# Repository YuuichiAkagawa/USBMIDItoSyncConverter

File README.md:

# USB MIDI to Sync Converter
Converts USB MIDI clock messages to sync signals.

[日本語版](README-ja.md)

## How to build
### Target microcontroller
- Seeed XIAO RP2040

### Build
This project uses Arduino IDE2 and requires the following libraries:
- board: [Arduino-pico](https://github.com/earlephilhower/arduino-pico) 4.1.1
- library: [Arduino MIDI Library](https://github.com/FortySevenEffects/arduino_midi_library) 5.0.2

Build setting:
- Tools->Board:->Raspberry Pi Pico/RP2040->Seed XIAO RP2040
- Tools->USB Stack:->Adafruilt TinyUSB

## Schematic
Complete schematic created in [KiCad](./hardware/KiCad/USBMIDItoSYNC_Converter/).

Minimum configuration with sync signal output terminal only

## Usage
Connects to the sending MIDI device with a USB cable and to the receiving device with a 3.5 mm stereo cable.  
The run mode switch can be used to select the action to be taken when a MIDI START/STOP message is received.

### Run mode switch
The D1 pin is assigned to mode switch. D1 is pulled up and goes High when open.

|D1 |behaviour|
|----|---------|
|Low |Sends out or stops the sync signal in conjunction with MIDI Start and Stop messages.|
|High|Free run. When MIDI Clock is received, the Sync signal is sent regardless of the playback status of the MIDI device.|

### DIN SYNC (experimental)
The DIN SYNC Start/Stop signal is output to the D2 pin.
D2 pin is assigned to 'DIN S' on the DIP switch and is connected to the RING of the Sync terminal.

### TRS MIDI In/Out (TypeA)
Transfers MIDI messages between USB MIDI and TRS MIDI.  
Note:
- SysEx is not supported.
- The clock input from TRS MIDI IN cannot be converted to a Sync signal.
  
### Setting switch
The setting switches can be used to set PPQ values and MIDI filter settings.  

|pin|name | setting             |
|---|-----|---------------------|
|D5 |MODE0|Type setting<br>L:PPQ values are changed using Setting switch. The value stored in the EEPROM is ignored.<br>H:PPQ values ​​are changed using SysEx messages. Settings are saved in EEPROM.
|D4 |MODE1|MODE0=L : PPQ selecter<br>MODE0=H : MIDI FilterSelector
|D3 |MODE2|MODE0=L : PPQ selecter<br>MODE0=H : MIDI FilterSelector

#### MODE0=0 PPQ selector
|MODE1 |MODE2 | PPQ    |
|------|------|--------|
|H(Off)|H(Off)|1       |
|H(Off)|L(On) |2       |
|L(On) |H(Off)|4       |
|L(On) |L(On) |24      |

#### MODE0=1 MIDI Filter
|MODE1 |MODE2 | Filter                                             |
|------|------|----------------------------------------------------|
|H(Off)|H(Off)|All messages are forwarded from USB to TRS MIDI Out |
|H(Off)|L(On) |Only Clock, Start, Stop, Continue are fowarded.     |
|L(On) |H(Off)|Foward only clocks                                  |
|L(On) |L(On) |N/A (Reserved)                                      |

## About the pulse width of the sync signal
In this project, the pulse width of the sync signal is set to 5 ms.  
The reason for this is that the KORG specification is 15 ms, but many other companies' devices use 5 ms.  
If you want to change this, modify the definition of ```DEFAULT_SPW``` to ```SPW_15MS``` and rebuild.

## Change the PPQ via SysEx message
The PPQ values can be changed using SysEx messages.  
You can specify a value between 1 and 24, but it will not work correctly unless it is a divisor of 24.  
The PPQ value is stored in the EEPROM at location 0x00.

|Byte[Hex] | Description                                     |
|:--------:|-------------------------------------------------|
|F0        | Exclusive Status                                |
|7E        | non realtime Universal System Exclusive Message |
|49        | Device ID                                       |
|0B        | File Reference Message                          |
|02        | Change (Select or Reselect)                     |
|nn        | PPQ : 1,2,3,4,6,8,0Ch(12),18h(24)               |
|F7        | End Of Exclusive                                |

## Change the Sync signal pulse width via SysEx message
The Sync signal pulse width can be changed using a SysEx message.  
It can be set to 5ms or 15ms.  
The Sync signal pulse width value is stored in the EEPROM at location 0x01.

|Byte[Hex] | Description                                             |
|:--------:|---------------------------------------------------------|
|F0        | Exclusive Status                                        |
|7E        | non realtime Universal System Exclusive Message         |
|49        | Device ID                                               |
|0B        | File Reference Message                                  |
|02        | Change (Select or Reselect)                             |
|nn        | Pulse Width 5ms:3Fh(63), 15ms:5Fh(95), Reserved:7Fh(127)|
|F7        | End Of Exclusive                                        |

SysEx files are stored in assets/sysex. Use as needed.

Note: The SysEx message does not define a dedicated one, but rather diverts the universal system-exclusive File Reference Message.

## License
USB MIDI to Sync Converter is open source and licensed under the [GPL3](/LICENSE) License.

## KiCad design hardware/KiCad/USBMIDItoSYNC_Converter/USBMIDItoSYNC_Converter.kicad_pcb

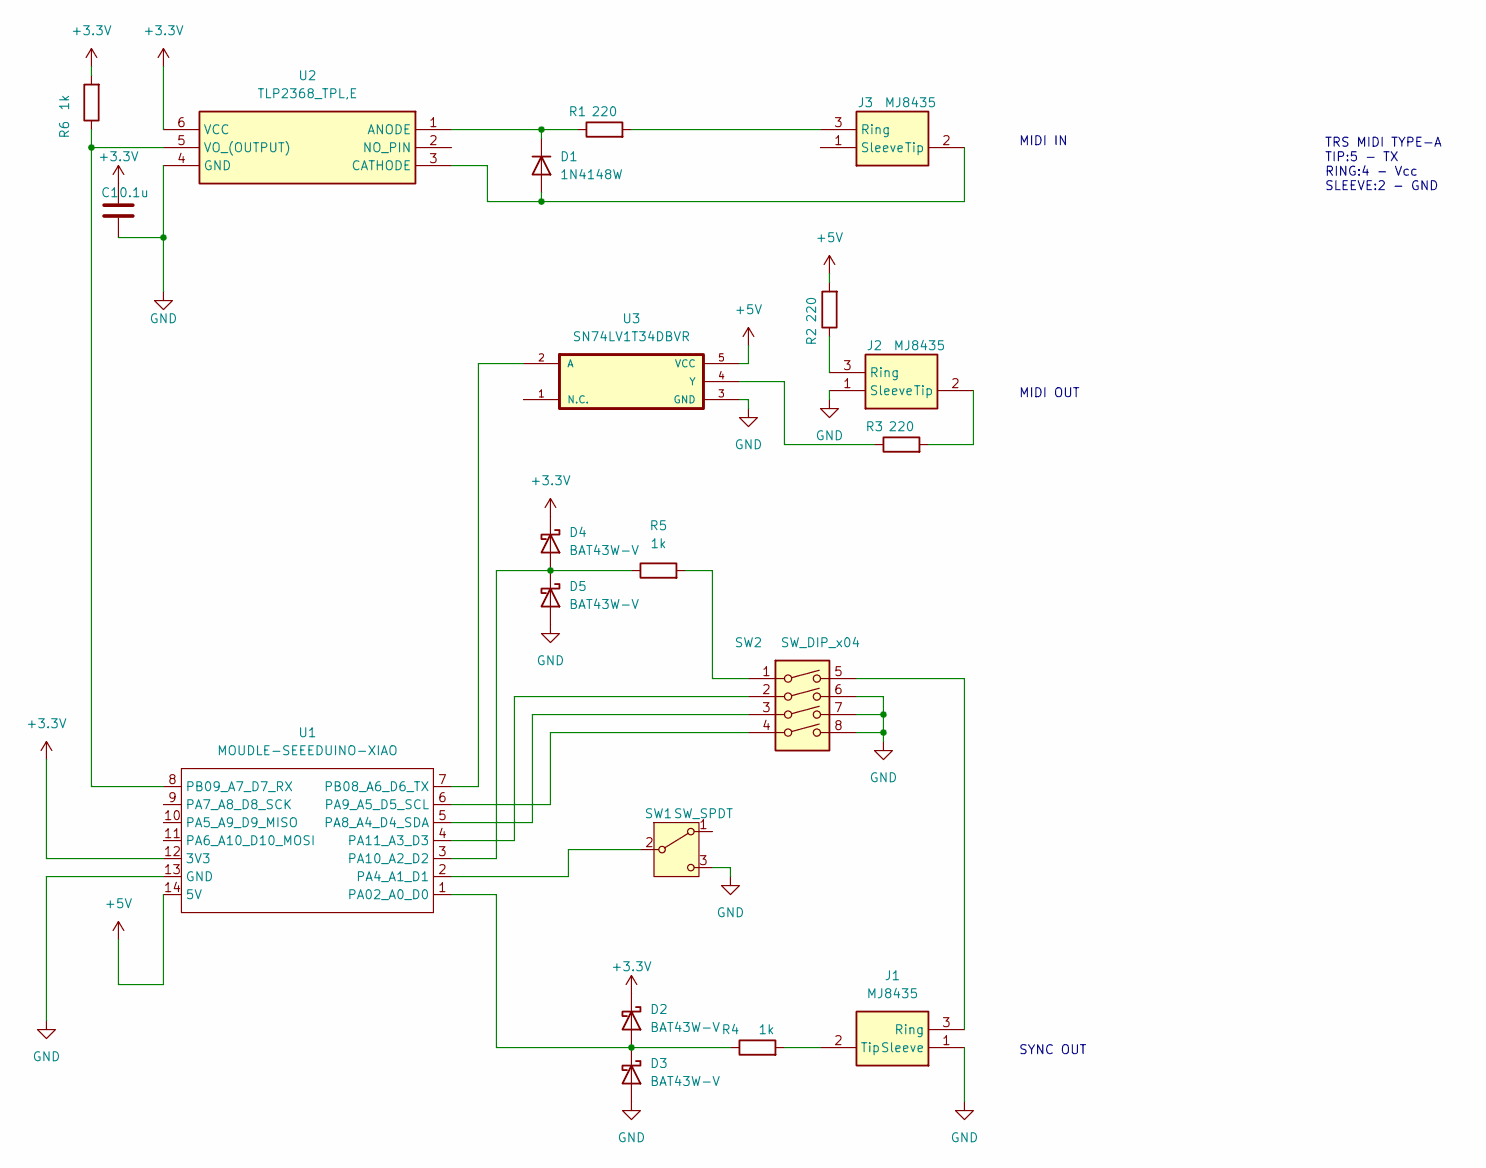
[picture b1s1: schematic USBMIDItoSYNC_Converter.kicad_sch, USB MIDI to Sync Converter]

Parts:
C1: 0.1u; C_0603_1608Metric
D1: 1N4148W; D_SOD-123
D2, D3, D4, D5: BAT43W-V; D_SOD-523
J1, J2, J3: MJ8435; Manufacturer_Part_Number MJ8435
R1, R2, R3: 220; R_0603_1608Metric
R4, R5, R6: 1k; R_0603_1608Metric
SW1: SW_SPDT; PinHeader_1x03_P2.54mm_Vertical
SW2: SW_DIP_x04; KHS42E
U1: MOUDLE-SEEEDUINO-XIAO; MOUDLE14P-XIAO-SMD-2.54-21X17.8MM
U2: TLP2368_TPL,E; SOIC127P700X230-6N; Manufacturer_Part_Number TLP2368(TPL,E; Mouser Part Number 757-TLP2368TPLE
U3: SN74LV1T34DBVR; SOT95P280X145-5N

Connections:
+3.3V: C1.1, D2.1 (K), D4.1 (K), R6.2, U1.12 (3V3), U2.6 (VCC)
+5V: R2.2, U1.14 (5V), U3.5 (VCC)
GND: C1.2, D3.2 (A), D5.2 (A), J1.1 (Sleeve), J2.1 (Sleeve), SW1.3 (C), SW2.6, SW2.7, SW2.8, U1.13 (GND), U2.4 (GND), U3.3 (GND)
unnamed: D1.2 (A), J3.2 (Tip), U2.3 (CATHODE)
unnamed: D1.1 (K), R1.1, U2.1 (ANODE)
unnamed: D2.2 (A), D3.1 (K), R4.1, U1.1 (PA02_A0_D0)
unnamed: D4.2 (A), D5.1 (K), R5.1, U1.3 (PA10_A2_D2)
unnamed: J1.3 (Ring), SW2.5
unnamed: J1.2 (Tip), R4.2
unnamed: J2.3 (Ring), R2.1
unnamed: J2.2 (Tip), R3.2
unnamed: J3.3 (Ring), R1.2
unnamed: R5.2, SW2.1
unnamed: SW1.2 (B), U1.2 (PA4_A1_D1)
unnamed: SW2.3, U1.5 (PA8_A4_D4_SDA)
unnamed: SW2.4, U1.6 (PA9_A5_D5_SCL)
unnamed: SW2.2, U1.4 (PA11_A3_D3)
unnamed: U1.7 (PB08_A6_D6_TX), U3.2 (A)
unnamed: R6.1, U1.8 (PB09_A7_D7_RX), U2.5 (VO_(OUTPUT))
unnamed: R3.1, U3.4 (Y)

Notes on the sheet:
MIDI IN
TRS MIDI TYPE-A TIP:5 - TX RING:4 - Vcc SLEEVE:2 - GND
SYNC OUT
MIDI OUT

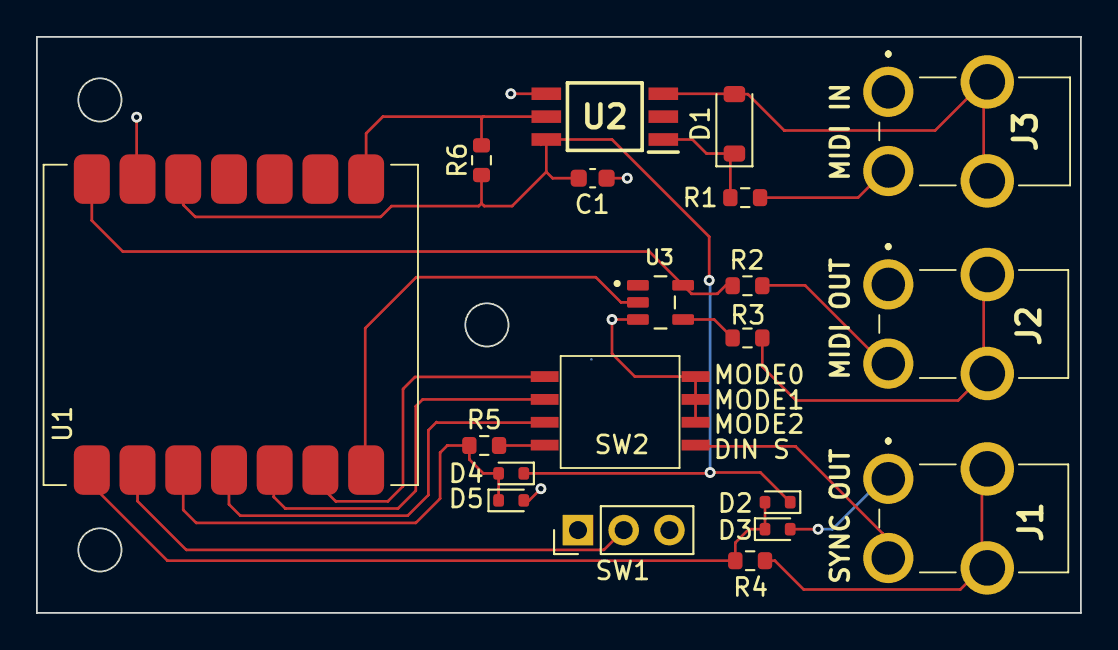
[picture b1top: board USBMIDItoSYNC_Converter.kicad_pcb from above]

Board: 2 copper layers, 58.0 x 32.0 mm, 20 parts (0 on the bottom side), 20 nets.

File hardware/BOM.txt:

# |  package |  parts    |
---+----------+-----------+--------------------------------------------------
U1 |          |XIAO RP2040|Seeed XIAO RP2040 board
U2 |SO6       |TLP2368    |Photo coupler (open collector output)
U3 |SOT3-5    |SN74LV1T34 |Single Power Supply BUFFER Logic Level Shifter
R1 |1608(0603)|220Ω      |Register
R2 |1608(0603)|220Ω      |Register
R3 |1608(0603)|220Ω      |Register
R4 |1608(0603)|1kΩ       |Register
R5 |1608(0603)|1kΩ       |Register
R6 |1608(0603)|1kΩ       |Register
C1 |1608(0603)|0.1uF      |Ceramic capacitor
D1 |SOD123    |1N4148W    |Switching Diode
D2 |SOD523    |BAT43XV2   |Shotkey Diode 30V200mA
D3 |SOD523    |BAT43XV2   |Shotkey Diode 30V200mA
D4 |SOD523    |BAT43XV2   |Shotkey Diode 30V200mA
D5 |SOD523    |BAT43XV2   |Shotkey Diode 30V200mA
J1 |          |MJ8435     |3.5mm Stereo mini jack
J2 |          |MJ8435     |3.5mm Stereo mini jack
J3 |          |MJ8435     |3.5mm Stereo mini jack
SW1|          |3P SW      |Slide Switch 1P2T Right Angle
SW2|SO8       |KHS42E     |DIP Switch 4P SMT
---+----------+-----------+--------------------------------------------------

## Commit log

2024-09-23 First working project
2024-09-24 fix the PPQ value with DIP switches
2024-10-13 Add case 3D model data
2024-10-13 fix schematic : protection circuit
2024-10-16 fix schematic : add OSHW logo
2024-10-27 Change: USB VID and PID
